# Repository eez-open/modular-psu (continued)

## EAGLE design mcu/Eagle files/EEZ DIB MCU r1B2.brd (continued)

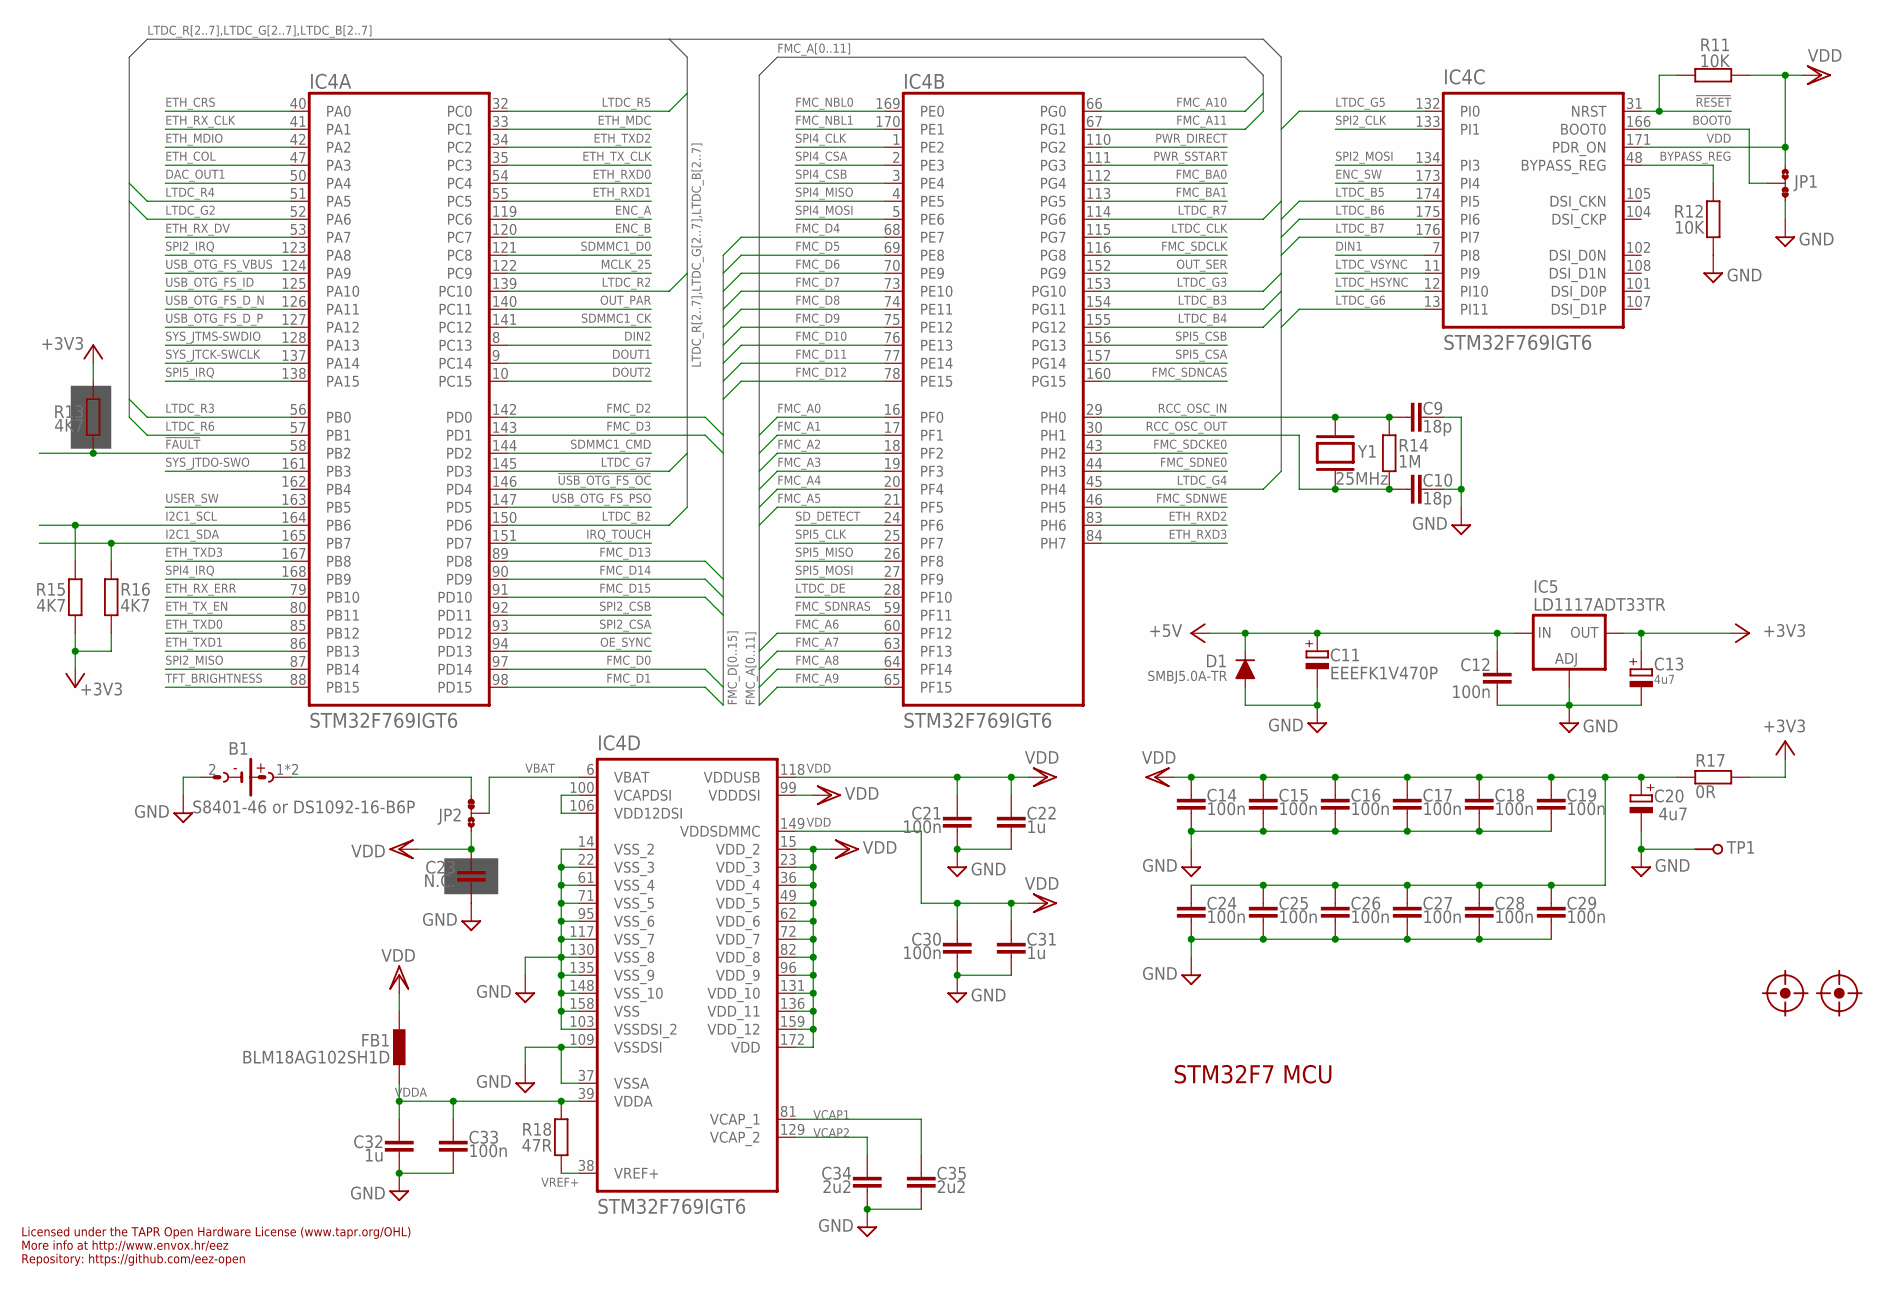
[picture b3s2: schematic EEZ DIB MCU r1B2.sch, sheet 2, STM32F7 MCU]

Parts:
B1: S8401-46 or DS1092-16-B6P; S8401-46
C9, C10: 18p; C0603
C11: EEEFK1V470P; CAPAE660X610N
C12, C14, C15, C16, C17, C18, C19, C21, C24, C25, C26, C27, C28, C29, C30, C33: 100n; C0603
C13, C20: 4u7; EC1206
C22, C31, C32: 1u; C0805
C23: N.C.; C0603
C34, C35: 2u2; C0805
D1: SMBJ5.0A-TR; DO214AA
FB1: BLM18AG102SH1D; BEAD0603
FM1, FM2: FIDUCIAL
IC4: STM32F769IGT6; LQFP-176_24X24MM
IC5: LD1117ADT33TR; DPACK
JP1, JP2: JP3-CUT
R11, R12: 10K; R0805
R13, R15, R16: 4K7; R0805
R14: 1M; R0805
R17: 0R; R0805
R18: 47R; R0805
TP1: PCB_TEST_TABSHIELD; PCB_SHIELD_TAB
Y1: 25MHz; HC-49/4H

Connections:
!FAULT: IC4.58 (PB2), R13.2; also elsewhere on the board
!RESET: IC4.31 (NRST), R11.2; also elsewhere on the board
!USB_OTG_FS_OC: IC4.146 (PD4); also elsewhere on the board
+3V3: C13.+, IC5.4 (OUT), R13.1, R15.1, R16.1, R17.1; also elsewhere on the board
+5V: C11.1 (+), C12.1, D1.C, IC5.3 (IN); also elsewhere on the board
BOOT0: IC4.166 (BOOT0), JP1.COM
BYPASS_REG: IC4.48 (BYPASS_REG), R12.2
DAC_OUT1: IC4.50 (PA4); also elsewhere on the board
DIN1: IC4.7 (PI8); also elsewhere on the board
DIN2: IC4.8 (PC13); also elsewhere on the board
DOUT1: IC4.9 (PC14); also elsewhere on the board
DOUT2: IC4.10 (PC15); also elsewhere on the board
ENC_A: IC4.119 (PC6); also elsewhere on the board
ENC_B: IC4.120 (PC7); also elsewhere on the board
ENC_SW: IC4.173 (PI4); also elsewhere on the board
ETH_COL: IC4.47 (PA3); also elsewhere on the board
ETH_CRS: IC4.40 (PA0); also elsewhere on the board
ETH_MDC: IC4.33 (PC1); also elsewhere on the board
ETH_MDIO: IC4.42 (PA2); also elsewhere on the board
ETH_RXD0: IC4.54 (PC4); also elsewhere on the board
ETH_RXD1: IC4.55 (PC5); also elsewhere on the board
ETH_RXD2: IC4.83 (PH6); also elsewhere on the board
ETH_RXD3: IC4.84 (PH7); also elsewhere on the board
ETH_RX_CLK: IC4.41 (PA1); also elsewhere on the board
ETH_RX_DV: IC4.53 (PA7); also elsewhere on the board
ETH_RX_ERR: IC4.79 (PB10); also elsewhere on the board
ETH_TXD0: IC4.85 (PB12); also elsewhere on the board
ETH_TXD1: IC4.86 (PB13); also elsewhere on the board
ETH_TXD2: IC4.34 (PC2); also elsewhere on the board
ETH_TXD3: IC4.167 (PB8); also elsewhere on the board
ETH_TX_CLK: IC4.35 (PC3); also elsewhere on the board
ETH_TX_EN: IC4.80 (PB11); also elsewhere on the board
FMC_A0: IC4.16 (PF0); also elsewhere on the board
FMC_A1: IC4.17 (PF1); also elsewhere on the board
FMC_A2: IC4.18 (PF2); also elsewhere on the board
FMC_A3: IC4.19 (PF3); also elsewhere on the board
FMC_A4: IC4.20 (PF4); also elsewhere on the board
FMC_A5: IC4.21 (PF5); also elsewhere on the board
FMC_A6: IC4.60 (PF12); also elsewhere on the board
FMC_A7: IC4.63 (PF13); also elsewhere on the board
FMC_A8: IC4.64 (PF14); also elsewhere on the board
FMC_A9: IC4.65 (PF15); also elsewhere on the board
FMC_A10: IC4.66 (PG0); also elsewhere on the board
FMC_A11: IC4.67 (PG1); also elsewhere on the board
FMC_BA0: IC4.112 (PG4); also elsewhere on the board
FMC_BA1: IC4.113 (PG5); also elsewhere on the board
FMC_D0: IC4.97 (PD14); also elsewhere on the board
FMC_D1: IC4.98 (PD15); also elsewhere on the board
FMC_D2: IC4.142 (PD0); also elsewhere on the board
FMC_D3: IC4.143 (PD1); also elsewhere on the board
FMC_D4: IC4.68 (PE7); also elsewhere on the board
FMC_D5: IC4.69 (PE8); also elsewhere on the board
FMC_D6: IC4.70 (PE9); also elsewhere on the board
FMC_D7: IC4.73 (PE10); also elsewhere on the board
FMC_D8: IC4.74 (PE11); also elsewhere on the board
FMC_D9: IC4.75 (PE12); also elsewhere on the board
FMC_D10: IC4.76 (PE13); also elsewhere on the board
FMC_D11: IC4.77 (PE14); also elsewhere on the board
FMC_D12: IC4.78 (PE15); also elsewhere on the board
FMC_D13: IC4.89 (PD8); also elsewhere on the board
FMC_D14: IC4.90 (PD9); also elsewhere on the board
FMC_D15: IC4.91 (PD10); also elsewhere on the board
FMC_NBL0: IC4.169 (PE0); also elsewhere on the board
FMC_NBL1: IC4.170 (PE1); also elsewhere on the board
FMC_SDCKE0: IC4.43 (PH2); also elsewhere on the board
FMC_SDCLK: IC4.116 (PG8); also elsewhere on the board
FMC_SDNCAS: IC4.160 (PG15); also elsewhere on the board
FMC_SDNE0: IC4.44 (PH3); also elsewhere on the board
FMC_SDNRAS: IC4.59 (PF11); also elsewhere on the board
FMC_SDNWE: IC4.46 (PH5); also elsewhere on the board
GND: B1.2 (-), C9.1, C10.1, C11.2 (-), C12.2, C13.-, C14.2, C15.2, C16.2, C17.2, C18.2, C19.2, C20.-, C21.2, C22.2, C23.2, C24.2, C25.2, C26.2, C27.2, C28.2, C29.2, C30.2, C31.2, C32.2, C33.2, C34.2, C35.2, D1.A, IC4.14 (VSS_2), IC4.22 (VSS_3), IC4.37 (VSSA), IC4.61 (VSS_4), IC4.71 (VSS_5), IC4.95 (VSS_6), IC4.103 (VSSDSI_2), IC4.109 (VSSDSI), IC4.117 (VSS_7), IC4.130 (VSS_8), IC4.135 (VSS_9), IC4.148 (VSS_10), IC4.158 (VSS), IC5.1 (ADJ), JP1.NC, R12.1, TP1.1; also elsewhere on the board
I2C1_SCL: IC4.164 (PB6), R15.2; also elsewhere on the board
I2C1_SDA: IC4.165 (PB7), R16.2; also elsewhere on the board
IRQ_TOUCH: IC4.151 (PD7); also elsewhere on the board
LTDC_B2: IC4.150 (PD6); also elsewhere on the board
LTDC_B3: IC4.154 (PG11); also elsewhere on the board
LTDC_B4: IC4.155 (PG12); also elsewhere on the board
LTDC_B5: IC4.174 (PI5); also elsewhere on the board
LTDC_B6: IC4.175 (PI6); also elsewhere on the board
LTDC_B7: IC4.176 (PI7); also elsewhere on the board
LTDC_CLK: IC4.115 (PG7); also elsewhere on the board
LTDC_DE: IC4.28 (PF10); also elsewhere on the board
LTDC_G2: IC4.52 (PA6); also elsewhere on the board
LTDC_G3: IC4.153 (PG10); also elsewhere on the board
LTDC_G4: IC4.45 (PH4); also elsewhere on the board
LTDC_G5: IC4.132 (PI0); also elsewhere on the board
LTDC_G6: IC4.13 (PI11); also elsewhere on the board
LTDC_G7: IC4.145 (PD3); also elsewhere on the board
LTDC_HSYNC: IC4.12 (PI10); also elsewhere on the board
LTDC_R2: IC4.139 (PC10); also elsewhere on the board
LTDC_R3: IC4.56 (PB0); also elsewhere on the board
LTDC_R4: IC4.51 (PA5); also elsewhere on the board
LTDC_R5: IC4.32 (PC0); also elsewhere on the board
LTDC_R6: IC4.57 (PB1); also elsewhere on the board
LTDC_R7: IC4.114 (PG6); also elsewhere on the board
LTDC_VSYNC: IC4.11 (PI9); also elsewhere on the board
MCLK_25: IC4.122 (PC9); also elsewhere on the board
unnamed: B1.1 (+), B1.3 (+), JP2.NC
unnamed: IC4.100 (VCAPDSI), IC4.106 (VDD12DSI)
OE_SYNC: IC4.94 (PD13); also elsewhere on the board
OUT_PAR: IC4.140 (PC11); also elsewhere on the board
OUT_SER: IC4.152 (PG9); also elsewhere on the board
PWR_DIRECT: IC4.110 (PG2); also elsewhere on the board
PWR_SSTART: IC4.111 (PG3); also elsewhere on the board
RCC_OSC_IN: C9.2, IC4.29 (PH0), R14.2, Y1.2
RCC_OSC_OUT: C10.2, IC4.30 (PH1), R14.1, Y1.1
SDMMC1_CK: IC4.141 (PC12); also elsewhere on the board
SDMMC1_CMD: IC4.144 (PD2); also elsewhere on the board
SDMMC1_D0: IC4.121 (PC8); also elsewhere on the board
SD_DETECT: IC4.24 (PF6); also elsewhere on the board
SPI2_CLK: IC4.133 (PI1); also elsewhere on the board
SPI2_CSA: IC4.93 (PD12); also elsewhere on the board
SPI2_CSB: IC4.92 (PD11); also elsewhere on the board
SPI2_IRQ: IC4.123 (PA8); also elsewhere on the board
SPI2_MISO: IC4.87 (PB14); also elsewhere on the board
SPI2_MOSI: IC4.134 (PI3); also elsewhere on the board
SPI4_CLK: IC4.1 (PE2); also elsewhere on the board
SPI4_CSA: IC4.2 (PE3); also elsewhere on the board
SPI4_CSB: IC4.3 (PE4); also elsewhere on the board
SPI4_IRQ: IC4.168 (PB9); also elsewhere on the board
SPI4_MISO: IC4.4 (PE5); also elsewhere on the board
SPI4_MOSI: IC4.5 (PE6); also elsewhere on the board
SPI5_CLK: IC4.25 (PF7); also elsewhere on the board
SPI5_CSA: IC4.157 (PG14); also elsewhere on the board
SPI5_CSB: IC4.156 (PG13); also elsewhere on the board
SPI5_IRQ: IC4.138 (PA15); also elsewhere on the board
SPI5_MISO: IC4.26 (PF8); also elsewhere on the board
SPI5_MOSI: IC4.27 (PF9); also elsewhere on the board
SYS_JTCK-SWCLK: IC4.137 (PA14); also elsewhere on the board
SYS_JTDO-SWO: IC4.161 (PB3); also elsewhere on the board
SYS_JTMS-SWDIO: IC4.128 (PA13); also elsewhere on the board
TFT_BRIGHTNESS: IC4.88 (PB15); also elsewhere on the board
USB_OTG_FS_D_N: IC4.126 (PA11); also elsewhere on the board
USB_OTG_FS_D_P: IC4.127 (PA12); also elsewhere on the board
USB_OTG_FS_ID: IC4.125 (PA10); also elsewhere on the board
USB_OTG_FS_PSO: IC4.147 (PD5); also elsewhere on the board
USB_OTG_FS_VBUS: IC4.124 (PA9); also elsewhere on the board
USER_SW: IC4.163 (PB5); also elsewhere on the board
VBAT: IC4.6 (VBAT), JP2.COM
VCAP1: C35.1, IC4.81 (VCAP_1)
VCAP2: C34.1, IC4.129 (VCAP_2)
VDD: C14.1, C15.1, C16.1, C17.1, C18.1, C19.1, C20.+, C21.1, C22.1, C23.1, C24.1, C25.1, C26.1, C27.1, C28.1, C29.1, C30.1, C31.1, FB1.P$1 (1), IC4.15 (VDD_2), IC4.23 (VDD_3), IC4.36 (VDD_4), IC4.49 (VDD_5), IC4.62 (VDD_6), IC4.72 (VDD_7), IC4.82 (VDD_8), IC4.96 (VDD_9), IC4.99 (VDDDSI), IC4.118 (VDDUSB), IC4.131 (VDD_10), IC4.136 (VDD_11), IC4.149 (VDDSDMMC), IC4.159 (VDD_12), IC4.171 (PDR_ON), IC4.172 (VDD), JP1.NO, JP2.NO, R11.1, R17.2
VDDA: C32.1, C33.1, FB1.P$2 (2), IC4.39 (VDDA), R18.2
VREF+: IC4.38 (VREF+), R18.1

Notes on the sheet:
Licensed under the TAPR Open Hardware License (www.tapr.org/OHL)
Repository: https://github.com/eez-open
More info at http://www.envox.hr/eez
STM32F7 MCU

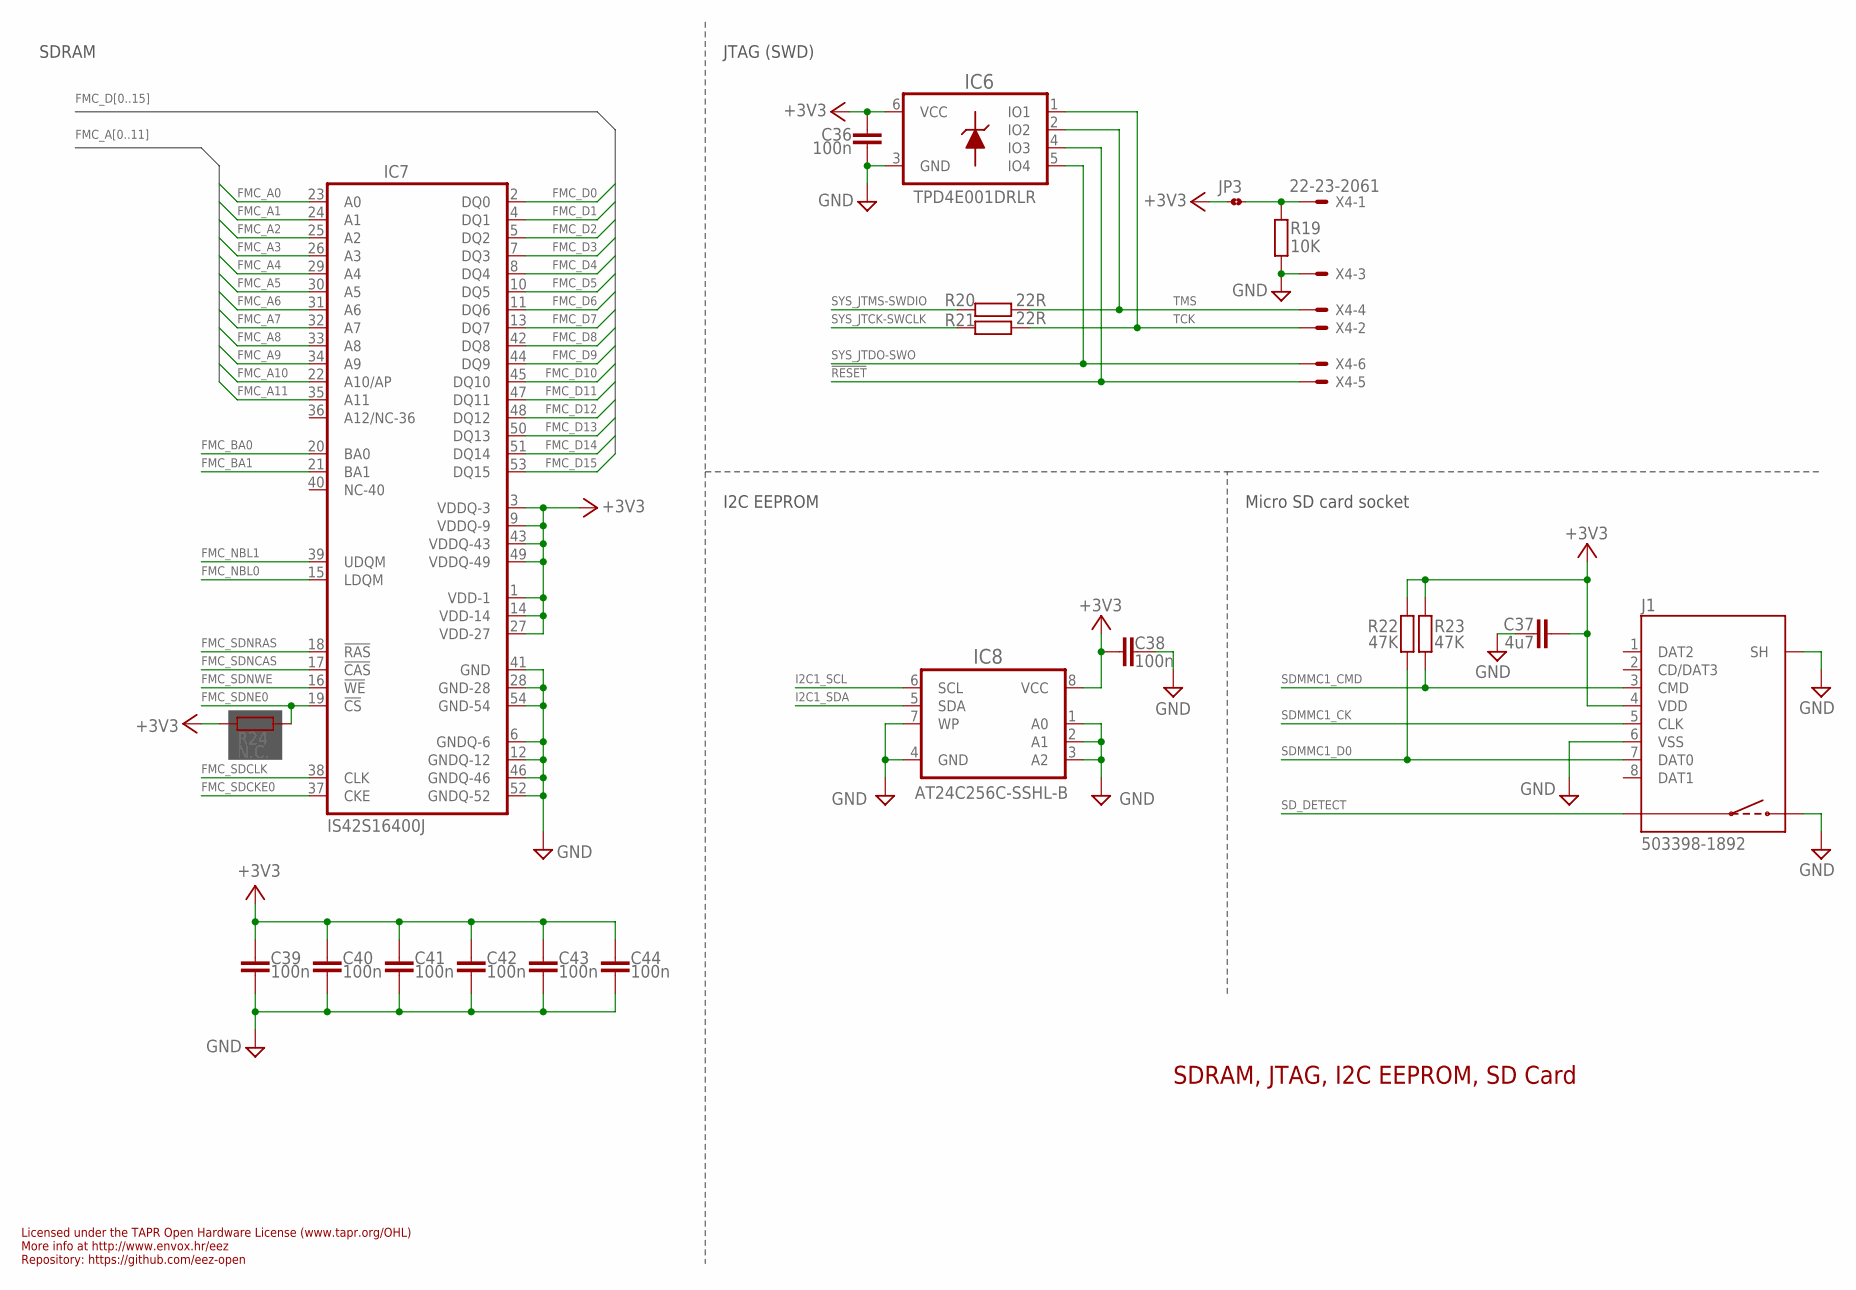
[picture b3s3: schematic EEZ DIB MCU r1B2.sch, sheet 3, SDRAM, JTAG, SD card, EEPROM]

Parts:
C36, C38, C39, C40, C41, C42, C43, C44: 100n; C0603
C37: 4u7; C1206
IC6: TPD4E001DRLR; DRL6
IC7: IS42S16400J; TSOPII-54
IC8: AT24C256C-SSHL-B; SOIC127P600X173-8N
J1: 503398-1892; 5033981892
JP3: JP2-CUT
R19: 10K; R0805
R20, R21: 22R; R0805
R22, R23: 47K; R0805
R24: N.C.; R0805
X4: 22-23-2061

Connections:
!RESET: IC6.4 (IO3), X4.5; also elsewhere on the board
+3V3: C36.1, C37.1, C38.2, C39.1, C40.1, C41.1, C42.1, C43.1, C44.1, IC6.6 (VCC), IC7.1 (VDD-1), IC7.3 (VDDQ-3), IC7.9 (VDDQ-9), IC7.14 (VDD-14), IC7.27 (VDD-27), IC7.43 (VDDQ-43), IC7.49 (VDDQ-49), IC8.8 (VCC), J1.4 (VDD), JP3.1, R22.1, R23.1, R24.1; also elsewhere on the board
FMC_A0: IC7.23 (A0); also elsewhere on the board
FMC_A1: IC7.24 (A1); also elsewhere on the board
FMC_A2: IC7.25 (A2); also elsewhere on the board
FMC_A3: IC7.26 (A3); also elsewhere on the board
FMC_A4: IC7.29 (A4); also elsewhere on the board
FMC_A5: IC7.30 (A5); also elsewhere on the board
FMC_A6: IC7.31 (A6); also elsewhere on the board
FMC_A7: IC7.32 (A7); also elsewhere on the board
FMC_A8: IC7.33 (A8); also elsewhere on the board
FMC_A9: IC7.34 (A9); also elsewhere on the board
FMC_A10: IC7.22 (A10/AP); also elsewhere on the board
FMC_A11: IC7.35 (A11); also elsewhere on the board
FMC_BA0: IC7.20 (BA0); also elsewhere on the board
FMC_BA1: IC7.21 (BA1); also elsewhere on the board
FMC_D0: IC7.2 (DQ0); also elsewhere on the board
FMC_D1: IC7.4 (DQ1); also elsewhere on the board
FMC_D2: IC7.5 (DQ2); also elsewhere on the board
FMC_D3: IC7.7 (DQ3); also elsewhere on the board
FMC_D4: IC7.8 (DQ4); also elsewhere on the board
FMC_D5: IC7.10 (DQ5); also elsewhere on the board
FMC_D6: IC7.11 (DQ6); also elsewhere on the board
FMC_D7: IC7.13 (DQ7); also elsewhere on the board
FMC_D8: IC7.42 (DQ8); also elsewhere on the board
FMC_D9: IC7.44 (DQ9); also elsewhere on the board
FMC_D10: IC7.45 (DQ10); also elsewhere on the board
FMC_D11: IC7.47 (DQ11); also elsewhere on the board
FMC_D12: IC7.48 (DQ12); also elsewhere on the board
FMC_D13: IC7.50 (DQ13); also elsewhere on the board
FMC_D14: IC7.51 (DQ14); also elsewhere on the board
FMC_D15: IC7.53 (DQ15); also elsewhere on the board
FMC_NBL0: IC7.15 (LDQM); also elsewhere on the board
FMC_NBL1: IC7.39 (UDQM); also elsewhere on the board
FMC_SDCKE0: IC7.37 (CKE); also elsewhere on the board
FMC_SDCLK: IC7.38 (CLK); also elsewhere on the board
FMC_SDNCAS: IC7.17 (!CAS); also elsewhere on the board
FMC_SDNE0: IC7.19 (!CS), R24.2; also elsewhere on the board
FMC_SDNRAS: IC7.18 (!RAS); also elsewhere on the board
FMC_SDNWE: IC7.16 (!WE); also elsewhere on the board
GND: C36.2, C37.2, C38.1, C39.2, C40.2, C41.2, C42.2, C43.2, C44.2, IC6.3 (GND), IC7.6 (GNDQ-6), IC7.12 (GNDQ-12), IC7.28 (GND-28), IC7.41 (GND), IC7.46 (GNDQ-46), IC7.52 (GNDQ-52), IC7.54 (GND-54), IC8.1 (A0), IC8.2 (A1), IC8.3 (A2), IC8.4 (GND), IC8.7 (WP), J1.6 (VSS), J1.S (SH), J1.SW2, R19.1, X4.3; also elsewhere on the board
I2C1_SCL: IC8.6 (SCL); also elsewhere on the board
I2C1_SDA: IC8.5 (SDA); also elsewhere on the board
unnamed: JP3.2, R19.2, X4.1
SDMMC1_CK: J1.5 (CLK); also elsewhere on the board
SDMMC1_CMD: J1.3 (CMD), R23.2; also elsewhere on the board
SDMMC1_D0: J1.7 (DAT0), R22.2; also elsewhere on the board
SD_DETECT: J1.SW1; also elsewhere on the board
SYS_JTCK-SWCLK: R21.1; also elsewhere on the board
SYS_JTDO-SWO: IC6.5 (IO4), X4.6; also elsewhere on the board
SYS_JTMS-SWDIO: R20.1; also elsewhere on the board
TCK: IC6.1 (IO1), R21.2, X4.2
TMS: IC6.2 (IO2), R20.2, X4.4

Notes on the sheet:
SDRAM, JTAG, I2C EEPROM, SD Card
Licensed under the TAPR Open Hardware License (www.tapr.org/OHL)
Repository: https://github.com/eez-open
More info at http://www.envox.hr/eez
I2C EEPROM
Micro SD card socket
JTAG (SWD)
SDRAM

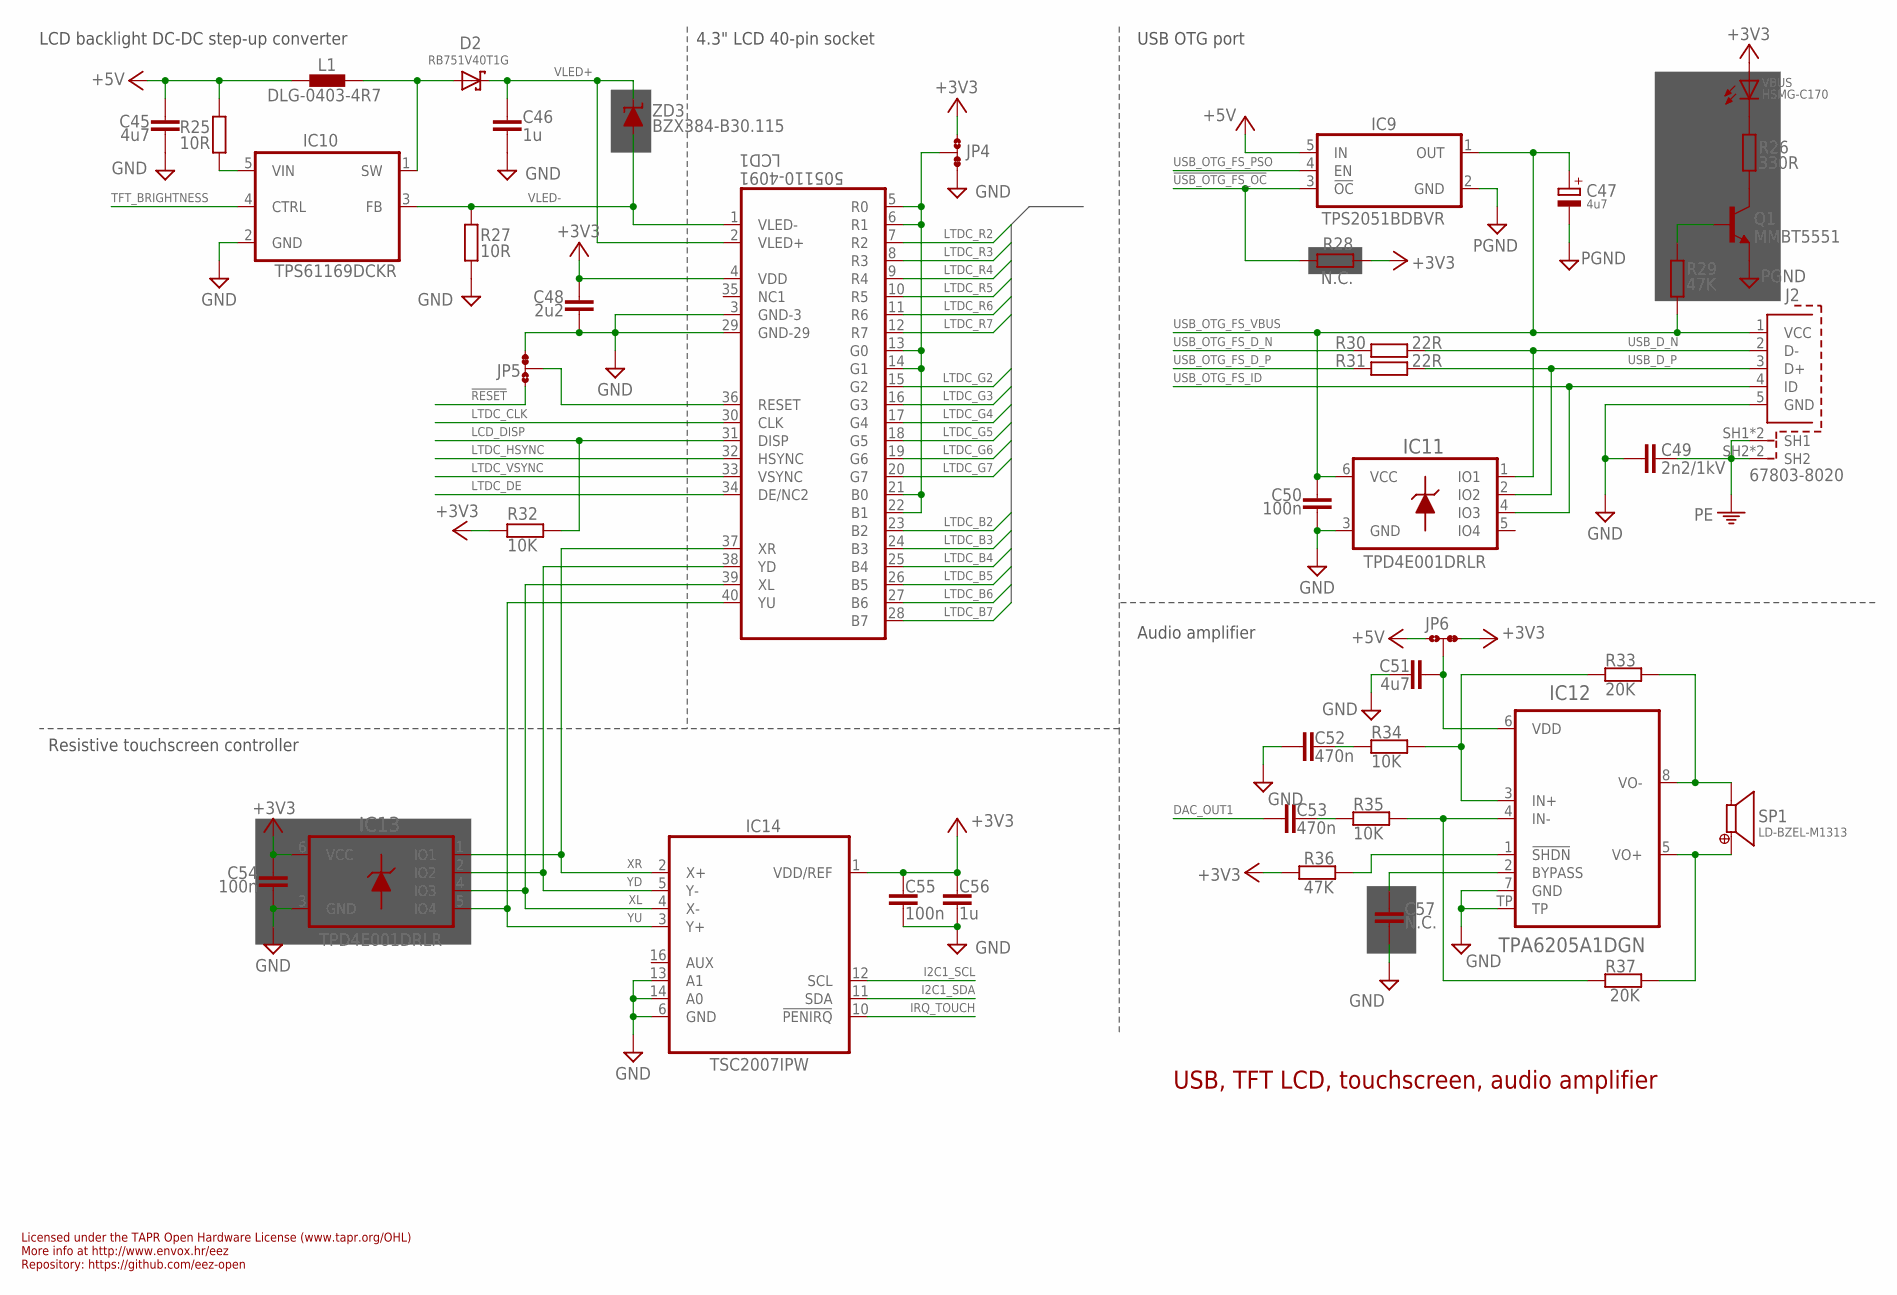
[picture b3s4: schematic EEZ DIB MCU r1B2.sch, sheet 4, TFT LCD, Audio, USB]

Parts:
C45, C51: 4u7; C1206
C46, C56: 1u; C0805
C47: 4u7; EC1206
C48: 2u2; C0805
C49: 2n2/1kV; C1210
C50, C54, C55: 100n; C0603
C52, C53: 470n; C0805
C57: N.C.; C0805
D2: RB751V40T1G; SOD323-R
IC9: TPS2051BDBVR; DBV5
IC10: TPS61169DCKR; DCK5
IC11, IC13: TPD4E001DRLR; DRL6
IC12: TPA6205A1DGN; SOP65P490X110-9N
IC14: TSC2007IPW; PW(R-PDSO-G16)
J2: 67803-8020; 678038020
JP4, JP5, JP6: JP3-CUT
L1: DLG-0403-4R7; DE0403
LCD1: 505110-4091; FPC_40
Q1: MMBT5551; SOT23-BEC
R25, R27: 10R; R0805
R26: 330R; R0805
R28: N.C.; R0805
R29, R36: 47K; R0805
R30, R31: 22R; R0805
R32, R34, R35: 10K; R0805
R33, R37: 20K; R0805
SP1: LD-BZEL-M1313
VBUS: HSMG-C170; LED_0805
ZD3: BZX384-B30.115; SOD323-W

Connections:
!AUDIO_SHDN: IC12.1 (!SHDN), R36.1
!RESET: JP5.NO; also elsewhere on the board
!USB_OTG_FS_OC: IC9.3 (!OC), R28.1; also elsewhere on the board
+3V3: C48.1, C54.2, C55.2, C56.2, IC13.6 (VCC), IC14.1 (VDD/REF), JP4.NO, JP6.NC, LCD1.4 (VDD), R28.2, R32.2, R36.2, VBUS.A; also elsewhere on the board
+5V: C45.1, IC9.5 (IN), JP6.NO, L1.1, R25.1; also elsewhere on the board
DAC_OUT1: C53.2; also elsewhere on the board
GND: C45.2, C46.2, C47.-, C48.2, C49.2, C50.1, C51.1, C52.2, C54.1, C55.1, C56.1, C57.1, IC9.2 (GND), IC10.2 (GND), IC11.3 (GND), IC12.7 (GND), IC12.TP, IC13.3 (GND), IC14.6 (GND), IC14.13 (A1), IC14.14 (A0), J2.5 (GND), JP4.NC, JP5.NC, LCD1.3 (GND-3), LCD1.29 (GND-29), Q1.E, R27.2; also elsewhere on the board
I2C1_SCL: IC14.12 (SCL); also elsewhere on the board
I2C1_SDA: IC14.11 (SDA); also elsewhere on the board
IRQ_TOUCH: IC14.10 (!PENIRQ); also elsewhere on the board
LCD_DISP: LCD1.31 (DISP), R32.1
LTDC_B2: LCD1.23 (B2); also elsewhere on the board
LTDC_B3: LCD1.24 (B3); also elsewhere on the board
LTDC_B4: LCD1.25 (B4); also elsewhere on the board
LTDC_B5: LCD1.26 (B5); also elsewhere on the board
LTDC_B6: LCD1.27 (B6); also elsewhere on the board
LTDC_B7: LCD1.28 (B7); also elsewhere on the board
LTDC_CLK: LCD1.30 (CLK); also elsewhere on the board
LTDC_DE: LCD1.34 (DE/NC2); also elsewhere on the board
LTDC_G2: LCD1.15 (G2); also elsewhere on the board
LTDC_G3: LCD1.16 (G3); also elsewhere on the board
LTDC_G4: LCD1.17 (G4); also elsewhere on the board
LTDC_G5: LCD1.18 (G5); also elsewhere on the board
LTDC_G6: LCD1.19 (G6); also elsewhere on the board
LTDC_G7: LCD1.20 (G7); also elsewhere on the board
LTDC_HSYNC: LCD1.32 (HSYNC); also elsewhere on the board
LTDC_R2: LCD1.7 (R2); also elsewhere on the board
LTDC_R3: LCD1.8 (R3); also elsewhere on the board
LTDC_R4: LCD1.9 (R4); also elsewhere on the board
LTDC_R5: LCD1.10 (R5); also elsewhere on the board
LTDC_R6: LCD1.11 (R6); also elsewhere on the board
LTDC_R7: LCD1.12 (R7); also elsewhere on the board
LTDC_VSYNC: LCD1.33 (VSYNC); also elsewhere on the board
unnamed: R26.2, VBUS.C
unnamed: JP4.COM, LCD1.5 (R0), LCD1.6 (R1), LCD1.13 (G0), LCD1.14 (G1), LCD1.21 (B0), LCD1.22 (B1)
unnamed: Q1.C, R26.1
unnamed: Q1.B, R29.2
unnamed: JP5.COM, LCD1.36 (RESET)
unnamed: IC10.5 (VIN), R25.2
unnamed: IC12.5 (VO+), R37.1, SP1.+
unnamed: C51.2, IC12.6 (VDD), JP6.COM
unnamed: IC12.8 (VO-), R33.1, SP1.-
unnamed: IC12.4 (IN-), R35.1, R37.2
unnamed: IC12.3 (IN+), R33.2, R34.1
unnamed: C52.1, R34.2
unnamed: C57.2, IC12.2 (BYPASS)
unnamed: C53.1, R35.2
PE: C49.1, J2.SH1, J2.SH1.1 (SH1), J2.SH2, J2.SH2.2 (SH2); also elsewhere on the board
SW_WLED: D2.A, IC10.1 (SW), L1.2
TFT_BRIGHTNESS: IC10.4 (CTRL); also elsewhere on the board
USB_D_N: IC11.1 (IO1), J2.2 (D-), R30.1
USB_D_P: IC11.2 (IO2), J2.3 (D+), R31.1
USB_OTG_FS_D_N: R30.2; also elsewhere on the board
USB_OTG_FS_D_P: R31.2; also elsewhere on the board
USB_OTG_FS_ID: IC11.4 (IO3), J2.4 (ID); also elsewhere on the board
USB_OTG_FS_PSO: IC9.4 (EN); also elsewhere on the board
USB_OTG_FS_VBUS: C47.+, C50.2, IC9.1 (OUT), IC11.6 (VCC), J2.1 (VCC), R29.1; also elsewhere on the board
VLED+: C46.1, D2.C, LCD1.2 (VLED+), ZD3.C
VLED-: IC10.3 (FB), LCD1.1 (VLED-), R27.1, ZD3.A
XL: IC13.4 (IO3), IC14.4 (X-), LCD1.39 (XL)
XR: IC13.1 (IO1), IC14.2 (X+), LCD1.37 (XR)
YD: IC13.2 (IO2), IC14.5 (Y-), LCD1.38 (YD)
YU: IC13.5 (IO4), IC14.3 (Y+), LCD1.40 (YU)

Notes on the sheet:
USB, TFT LCD, touchscreen, audio amplifier
Licensed under the TAPR Open Hardware License (www.tapr.org/OHL)
Repository: https://github.com/eez-open
More info at http://www.envox.hr/eez
4.3" LCD 40-pin socket
LCD backlight DC-DC step-up converter
USB OTG port
Resistive touchscreen controller
Audio amplifier

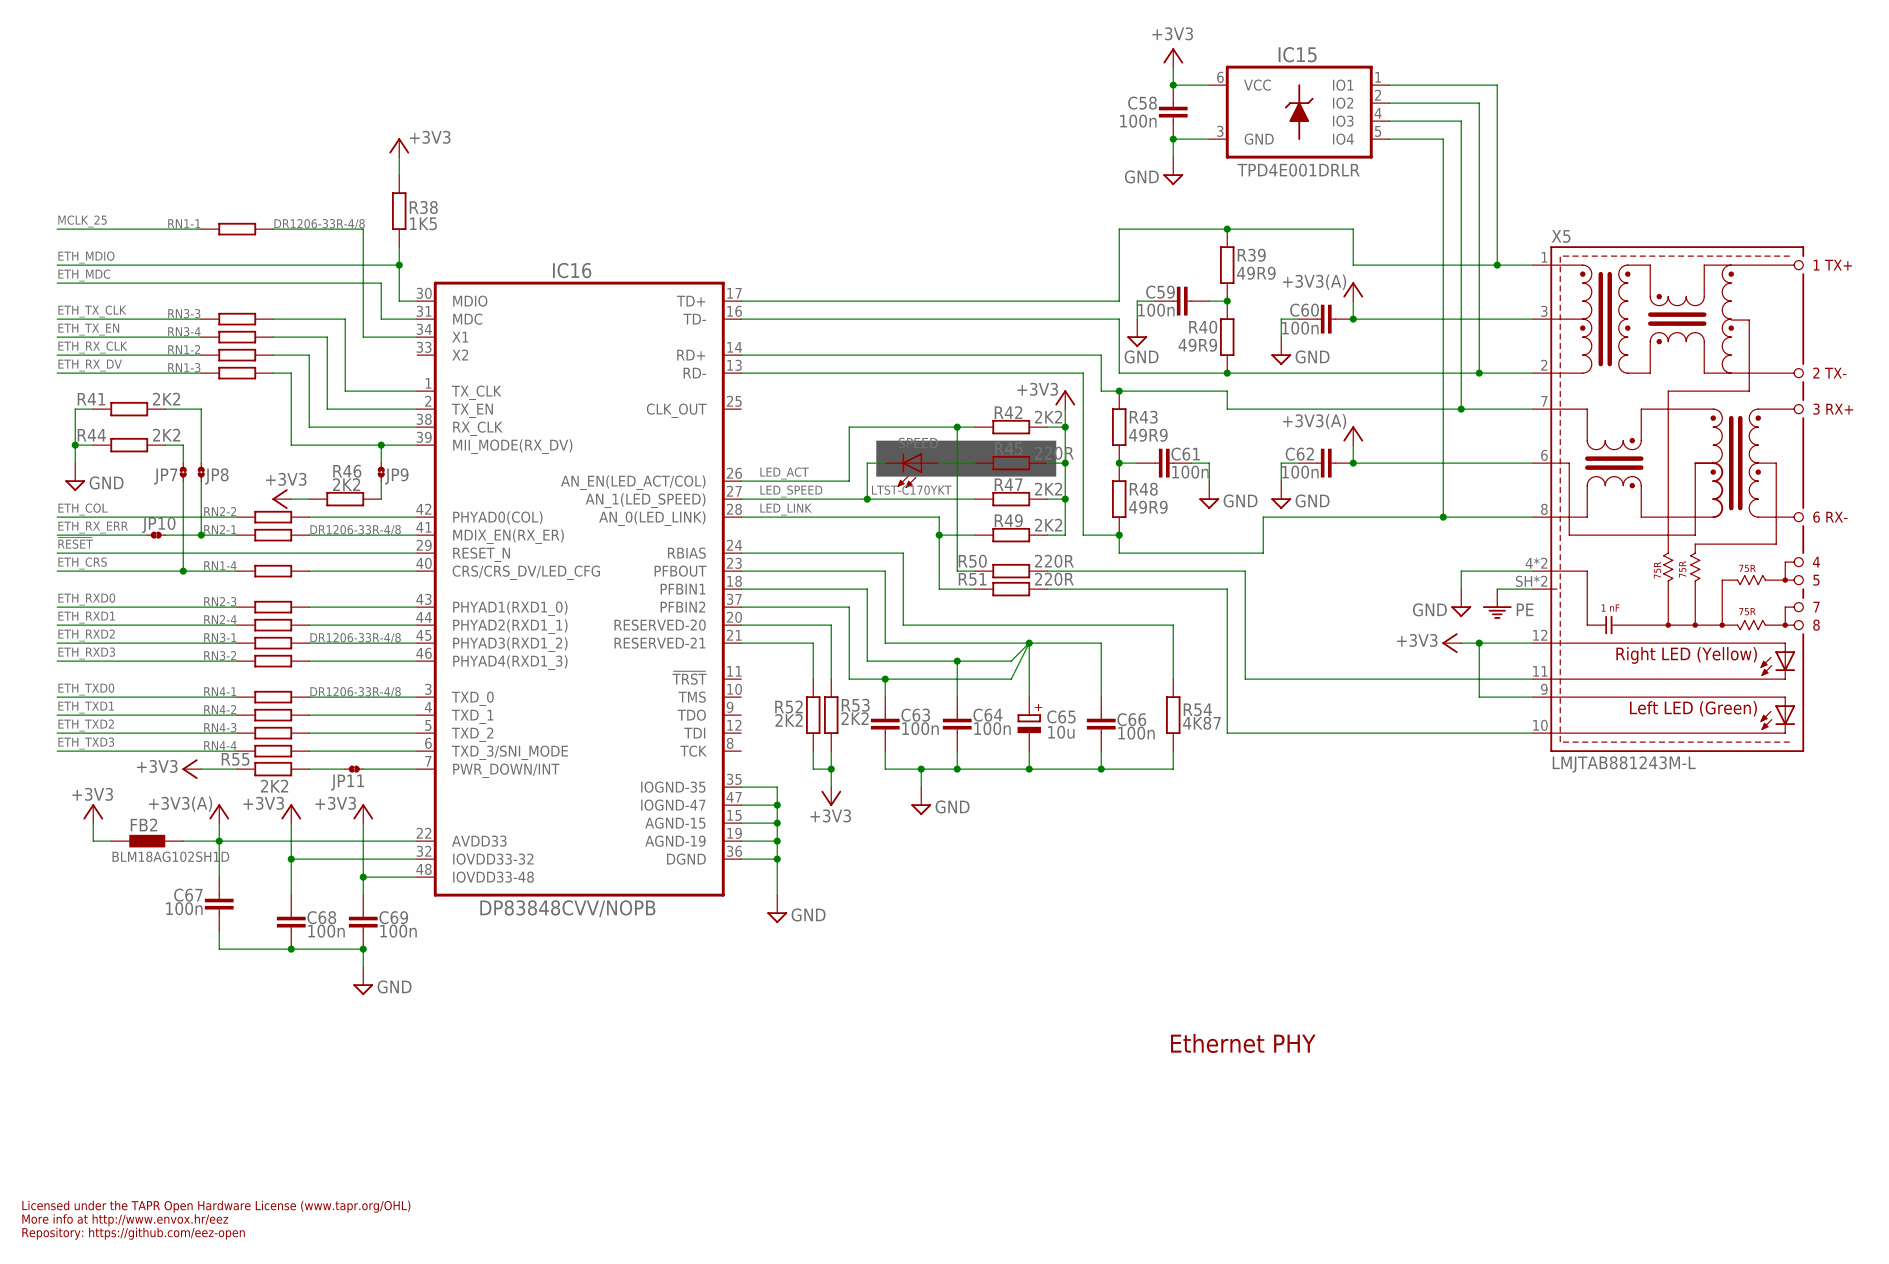
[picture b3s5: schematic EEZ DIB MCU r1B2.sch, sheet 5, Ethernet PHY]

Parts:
C58, C59, C60, C61, C62, C63, C64, C66, C67, C68, C69: 100n; C0603
C65: 10u; EC1206
FB2: BLM18AG102SH1D; BEAD0603
IC15: TPD4E001DRLR; DRL6
IC16: DP83848CVV/NOPB; PT48
JP7, JP8, JP9: JP2-CUT
JP10, JP11: JP2-NOCUT
R38: 1K5; R0805
R39, R40, R43, R48: 49R9; R0805
R41, R42, R44, R46, R47, R49, R52, R53, R55: 2K2; R0805
R45, R50, R51: 220R; R0805
R54: 4K87; R0805
RN1, RN2, RN3, RN4: DR1206-33R-4/8; CAY16
SPEED: LTST-C170YKT; LED_0805
X5: LMJTAB881243M-L; RJ45-TRAFO-LED

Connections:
!RESET: IC16.29 (RESET_N); also elsewhere on the board
+3V3: C58.1, C68.1, C69.1, FB2.P$1 (1), IC15.6 (VCC), IC16.32 (IOVDD33-32), IC16.48 (IOVDD33-48), R38.2, R42.1, R45.1, R46.1, R47.1, R49.1, R52.1, R53.1, R55.1, X5.9 (GREEN-A), X5.12 (YELLOW_A); also elsewhere on the board
+3V3(A): C60.2, C62.2, C67.1, FB2.P$2 (2), IC16.22 (AVDD33), X5.3 (CT), X5.6 (CR)
ETH_COL: RN2.2 (1); also elsewhere on the board
ETH_CRS: JP7.1, RN1.4 (1); also elsewhere on the board
ETH_MDC: IC16.31 (MDC); also elsewhere on the board
ETH_MDIO: IC16.30 (MDIO), R38.1; also elsewhere on the board
ETH_RXD0: RN2.3 (1); also elsewhere on the board
ETH_RXD1: RN2.4 (1); also elsewhere on the board
ETH_RXD2: RN3.1; also elsewhere on the board
ETH_RXD3: RN3.2 (1); also elsewhere on the board
ETH_RX_CLK: RN1.2 (1); also elsewhere on the board
ETH_RX_DV: RN1.3 (1); also elsewhere on the board
ETH_RX_ER: JP8.1, JP10.1, RN2.1
ETH_RX_ERR: JP10.2; also elsewhere on the board
ETH_TXD0: RN4.1; also elsewhere on the board
ETH_TXD1: RN4.2 (1); also elsewhere on the board
ETH_TXD2: RN4.3 (1); also elsewhere on the board
ETH_TXD3: RN4.4 (1); also elsewhere on the board
ETH_TX_CLK: RN3.3 (1); also elsewhere on the board
ETH_TX_EN: RN3.4 (1); also elsewhere on the board
GND: C58.2, C59.2, C60.1, C61.2, C62.1, C63.2, C64.2, C65.-, C66.2, C67.2, C68.2, C69.2, IC15.3 (GND), IC16.15 (AGND-15), IC16.19 (AGND-19), IC16.35 (IOGND-35), IC16.36 (DGND), IC16.47 (IOGND-47), R41.1, R44.1, R54.1, X5.4 (GND), X5.5 (GND); also elsewhere on the board
LED_ACT: IC16.26 (AN_EN(LED_ACT/COL)), R42.2, R50.2
LED_LINK: IC16.28 (AN_0(LED_LINK)), R49.2, R51.2
LED_SPEED: IC16.27 (AN_1(LED_SPEED)), R47.2, SPEED.C
MCLK_25: RN1.1; also elsewhere on the board
unnamed: IC16.1 (TX_CLK), RN3.6 (2)
unnamed: C59.1, R39.1, R40.2
unnamed: R50.1, X5.11 (YELLOW-C)
unnamed: R51.1, X5.10 (GREEN-C)
unnamed: IC16.2 (TX_EN), RN3.5 (2)
unnamed: IC16.39 (MII_MODE(RX_DV)), JP9.2, RN1.6 (2)
unnamed: IC16.38 (RX_CLK), RN1.7 (2)
unnamed: IC16.3 (TXD_0), RN4.8 (2)
unnamed: IC16.4 (TXD_1), RN4.7 (2)
unnamed: IC16.5 (TXD_2), RN4.6 (2)
unnamed: IC16.34 (X1), RN1.8 (2)
unnamed: JP9.1, R46.2
unnamed: JP7.2, R44.2
unnamed: JP8.2, R41.2
unnamed: IC16.7 (PWR_DOWN/INT), JP11.2
unnamed: JP11.1, R55.2
unnamed: IC16.6 (TXD_3/SNI_MODE), RN4.5 (2)
unnamed: IC16.46 (PHYAD4(RXD1_3)), RN3.7 (2)
unnamed: IC16.45 (PHYAD3(RXD1_2)), RN3.8 (2)
unnamed: IC16.42 (PHYAD0(COL)), RN2.7 (2)
unnamed: IC16.44 (PHYAD2(RXD1_1)), RN2.5 (2)
unnamed: IC16.43 (PHYAD1(RXD1_0)), RN2.6 (2)
unnamed: IC16.41 (MDIX_EN(RX_ER)), RN2.8 (2)
unnamed: IC16.40 (CRS/CRS_DV/LED_CFG), RN1.5 (2)
unnamed: IC16.24 (RBIAS), R54.2
unnamed: IC16.21 (RESERVED-21), R52.2
unnamed: IC16.20 (RESERVED-20), R53.2
unnamed: R45.2, SPEED.A
unnamed: C61.1, R43.1, R48.2
PE: X5.SH, X5.SH2 (SH); also elsewhere on the board
PFBOUT: C63.1, C64.1, C65.+, C66.1, IC16.18 (PFBIN1), IC16.23 (PFBOUT), IC16.37 (PFBIN2)
RD+: IC15.4 (IO3), IC16.14 (RD+), R43.2, X5.7 (RD+)
RD-: IC15.5 (IO4), IC16.13 (RD-), R48.1, X5.8 (RD-)
TD+: IC15.1 (IO1), IC16.17 (TD+), R39.2, X5.1 (TD+)
TD-: IC15.2 (IO2), IC16.16 (TD-), R40.1, X5.2 (TD-)

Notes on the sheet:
Ethernet PHY
Licensed under the TAPR Open Hardware License (www.tapr.org/OHL)
Repository: https://github.com/eez-open
More info at http://www.envox.hr/eez
